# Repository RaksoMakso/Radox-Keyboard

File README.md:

# Radox-Keyboard
## Idea taken from: https://github.com/mattdibi/redox-keyboard
Ergonomic Split Mechanical Keyboard
// Work in progress//

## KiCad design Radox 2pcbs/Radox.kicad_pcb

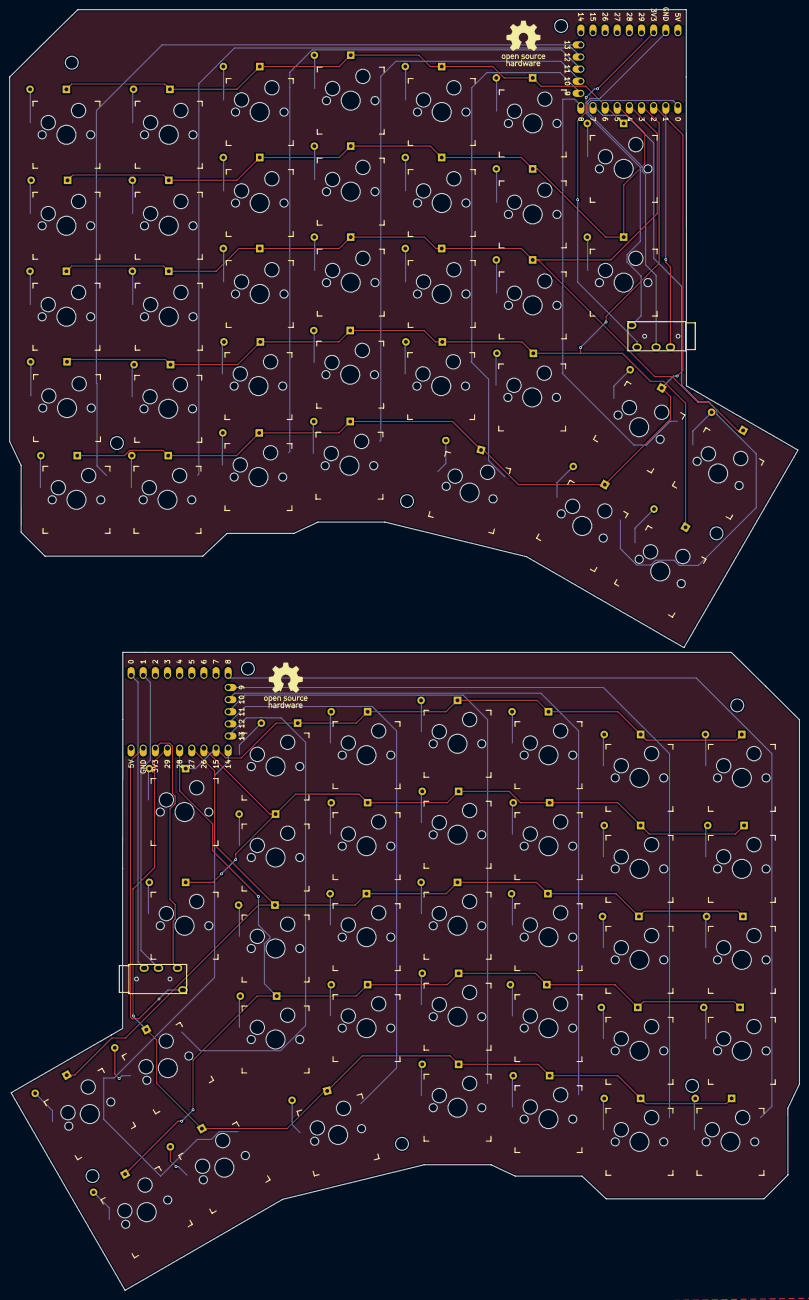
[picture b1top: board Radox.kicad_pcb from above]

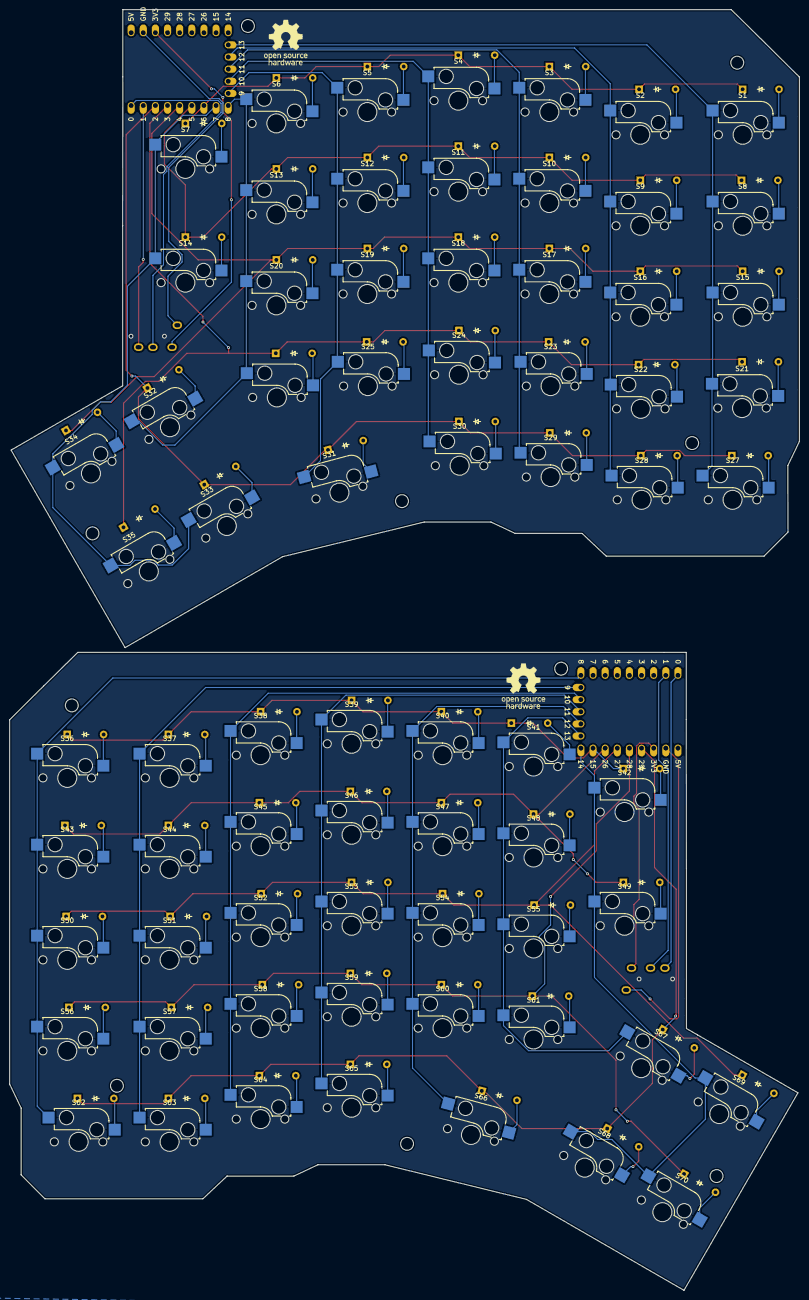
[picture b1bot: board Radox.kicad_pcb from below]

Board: 2 copper layers, 165.3 x 268.1 mm, 144 parts (70 on the bottom side), 102 nets.

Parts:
D1, D2, D3, D4, D5, D6, D7, D8, D9, D10, D11, D12, D13, D14, D15, D16, D17, D18, D19, D20, D21, D22, D23, D24, D25, D26, D27, D28, D29, D30, D31, D32, D33, D34, D35, D36, D37, D38, D39, D40, D41, D42, D43, D44, D45, D46, D47, D48, D49, D50, D51, D52, D53, D54, D55, D56, D57, D58, D59, D60, D61, D62, D63, D64, D65, D66, D67, D68, D69, D70: 1N4148; Diode_DO-35
S1, S2, S3, S4, S5, S6, S7, S8, S9, S10, S11, S12, S13, S14, S15, S16, S17, S18, S19, S20, S21, S22, S23, S24, S25, S26, S27, S28, S29, S30, S31, S32, S33, S34, S35, S36, S37, S38, S39, S40, S41, S42, S43, S44, S45, S46, S47, S48, S49, S50, S51, S52, S53, S54, S55, S56, S57, S58, S59, S60, S61, S62, S63, S64, S65, S66, S67, S68, S69, S70: Kailh_socket_MX
U1, U4: TRRS; TRRS_PJ-320A
U2, U3: RP2040_Zero

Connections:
/Column 0l: S1.1, S8.1, S15.1, S21.1, S27.1, U3.14 (13)
/Column 1l: S2.1, S9.1, S16.1, S22.1, S28.1, U3.13 (12)
/Column 2l: S3.1, S10.1, S17.1, S23.1, S29.1, U3.12 (11)
/Column 3l: S4.1, S11.1, S18.1, S24.1, S30.1, U3.11 (10)
/Column 4l: S5.1, S12.1, S19.1, S25.1, S31.1, U3.10 (9)
/Column 5l: S6.1, S13.1, S20.1, S26.1, S32.1, U3.9 (8)
/Column 6l: S7.1, S14.1, S33.1, S34.1, S35.1, U3.8 (7)
/Row 0l: D1.1 (K), D2.1 (K), D3.1 (K), D4.1 (K), D5.1 (K), D6.1 (K), D7.1 (K), U3.7 (6)
/Row 1l: D8.1 (K), D9.1 (K), D10.1 (K), D11.1 (K), D12.1 (K), D13.1 (K), D14.1 (K), U3.6 (5)
/Row 2l: D15.1 (K), D16.1 (K), D17.1 (K), D18.1 (K), D19.1 (K), D20.1 (K), D34.1 (K), U3.5 (4)
/Row 3l: D21.1 (K), D22.1 (K), D23.1 (K), D24.1 (K), D25.1 (K), D26.1 (K), D35.1 (K), U3.4 (3)
/Row 4l: D27.1 (K), D28.1 (K), D29.1 (K), D30.1 (K), D31.1 (K), D32.1 (K), D33.1 (K), U3.3 (2)
/column 0: S42.1, S49.1, S68.1, S69.1, S70.1, U2.15 (14)
/column 1: S41.1, S48.1, S55.1, S61.1, S67.1, U2.14 (13)
/column 2: S40.1, S47.1, S54.1, S60.1, S66.1, U2.13 (12)
/column 3: S39.1, S46.1, S53.1, S59.1, S65.1, U2.12 (11)
/column 4: S38.1, S45.1, S52.1, S58.1, S64.1, U2.11 (10)
/column 5: S37.1, S44.1, S51.1, S57.1, S63.1, U2.10 (9)
/column 6: S36.1, S43.1, S50.1, S56.1, S62.1, U2.9 (8)
/row 0: D36.1 (K), D37.1 (K), D38.1 (K), D39.1 (K), D40.1 (K), D41.1 (K), D42.1 (K), U2.16 (15)
/row 1: D43.1 (K), D44.1 (K), D45.1 (K), D46.1 (K), D47.1 (K), D48.1 (K), D49.1 (K), U2.17 (26)
/row 2: D50.1 (K), D51.1 (K), D52.1 (K), D53.1 (K), D54.1 (K), D55.1 (K), D69.1 (K), U2.18 (27)
/row 3: D56.1 (K), D57.1 (K), D58.1 (K), D59.1 (K), D60.1 (K), D61.1 (K), D70.1 (K), U2.19 (28)
/row 4: D62.1 (K), D63.1 (K), D64.1 (K), D65.1 (K), D66.1 (K), D67.1 (K), D68.1 (K), U2.20 (29)
unnamed: D1.2 (A), S1.2
unnamed: D2.2 (A), S2.2
unnamed: D3.2 (A), S3.2
unnamed: D4.2 (A), S4.2
unnamed: D5.2 (A), S5.2
unnamed: D6.2 (A), S6.2
unnamed: D7.2 (A), S7.2
unnamed: D8.2 (A), S8.2
unnamed: D9.2 (A), S9.2
unnamed: D10.2 (A), S10.2
unnamed: D11.2 (A), S11.2
unnamed: D12.2 (A), S12.2
unnamed: D13.2 (A), S13.2
unnamed: D14.2 (A), S14.2
unnamed: D15.2 (A), S15.2
unnamed: D16.2 (A), S16.2
unnamed: D17.2 (A), S17.2
unnamed: D18.2 (A), S18.2
unnamed: D19.2 (A), S19.2
unnamed: D20.2 (A), S20.2
unnamed: D21.2 (A), S21.2
unnamed: D22.2 (A), S22.2
unnamed: D23.2 (A), S23.2
unnamed: D24.2 (A), S24.2
unnamed: D25.2 (A), S25.2
unnamed: D26.2 (A), S26.2
unnamed: D27.2 (A), S27.2
unnamed: D28.2 (A), S28.2
unnamed: D29.2 (A), S29.2
unnamed: D30.2 (A), S30.2
unnamed: D31.2 (A), S31.2
unnamed: D32.2 (A), S32.2
unnamed: D33.2 (A), S33.2
unnamed: D34.2 (A), S34.2
unnamed: D35.2 (A), S35.2
unnamed: D36.2 (A), S36.2
unnamed: D37.2 (A), S37.2
unnamed: D38.2 (A), S38.2
unnamed: D39.2 (A), S39.2
unnamed: D40.2 (A), S40.2
unnamed: D41.2 (A), S41.2
unnamed: D42.2 (A), S42.2
unnamed: D43.2 (A), S43.2
unnamed: D44.2 (A), S44.2
unnamed: D45.2 (A), S45.2
unnamed: D46.2 (A), S46.2
unnamed: D47.2 (A), S47.2
unnamed: D48.2 (A), S48.2
unnamed: D49.2 (A), S49.2
unnamed: D50.2 (A), S50.2
unnamed: D51.2 (A), S51.2
unnamed: D52.2 (A), S52.2
unnamed: D53.2 (A), S53.2
unnamed: D54.2 (A), S54.2
unnamed: D55.2 (A), S55.2
unnamed: D56.2 (A), S56.2
unnamed: D57.2 (A), S57.2
unnamed: D58.2 (A), S58.2
unnamed: D59.2 (A), S59.2
unnamed: D60.2 (A), S60.2
unnamed: D61.2 (A), S61.2
unnamed: D62.2 (A), S62.2
unnamed: D63.2 (A), S63.2
unnamed: D64.2 (A), S64.2
unnamed: D65.2 (A), S65.2
unnamed: D66.2 (A), S66.2
unnamed: D67.2 (A), S67.2
unnamed: D68.2 (A), S68.2
unnamed: D69.2 (A), S69.2
unnamed: D70.2 (A), S70.2
unnamed: U1.3 (RING1), U2.2 (1)
unnamed: U1.4 (RING2), U2.1 (0)
unnamed: U1.1 (SLEEVE), U2.22 (GND)
unnamed: U1.2 (TIP), U2.21 (3V3)
unnamed: U3.1 (0), U4.3 (RING1)
unnamed: U3.2 (1), U4.4 (RING2)
unnamed: U3.21 (3V3), U4.2 (TIP)
unnamed: U3.22 (GND), U4.1 (SLEEVE)

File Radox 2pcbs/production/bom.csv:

Designator,Footprint,Quantity,Value,LCSC Part #
"D1, D10, D11, D12, D13, D14, D15, D16, D17, D18, D19, D2, D20, D21, D22, D23, D24, D25, D26, D27, D28, D29, D3, D30, D31, D32, D33, D34, D35, D36, D37, D38, D39, D4, D40, D41, D42, D43, D44, D45, D46, D47, D48, D49, D5, D50, D51, D52, D53, D54, D55, D56, D57, D58, D59, D6, D60, D61, D62, D63, D64, D65, D66, D67, D68, D69, D7, D70, D8, D9",Diode_DO-35,70,1N4148,
"S1, S10, S11, S12, S13, S14, S15, S16, S17, S18, S19, S2, S20, S21, S22, S23, S24, S25, S26, S27, S28, S29, S3, S30, S31, S32, S33, S34, S35, S36, S37, S38, S39, S4, S40, S41, S42, S43, S44, S45, S46, S47, S48, S49, S5, S50, S51, S52, S53, S54, S55, S56, S57, S58, S59, S6, S60, S61, S62, S63, S64, S65, S66, S67, S68, S69, S7, S70, S8, S9",Kailh_socket_MX,70,~,
"U1, U4",TRRS_PJ-320A,2,TRRS,
"U2, U3",RP2040_Zero,2,RP2040_Zero,
